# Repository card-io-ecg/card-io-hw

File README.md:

Card/IO hardware
================

Card/IO is an open source, single lead ECG in a business card-like format.

The project contains two PCB designs, created using KiCAD 7:
 
 - main_board: main/carrier board, which is a 4 layer PCB containing the MCU, display, battery and related circuitry
 - frontend: the ECG frontend, ADC, and touch detection/wakeup generator, implemented as a solder-on daughter board

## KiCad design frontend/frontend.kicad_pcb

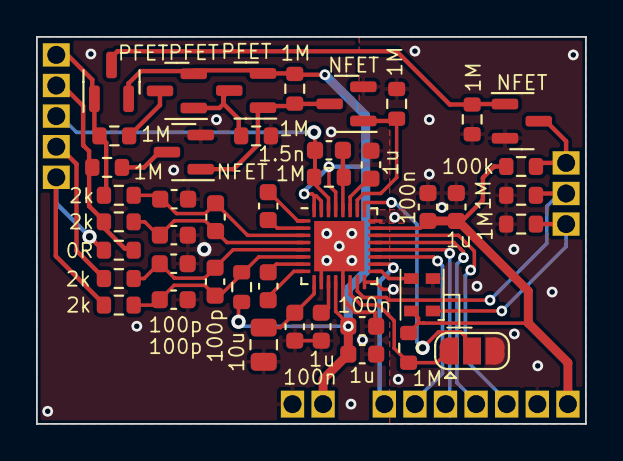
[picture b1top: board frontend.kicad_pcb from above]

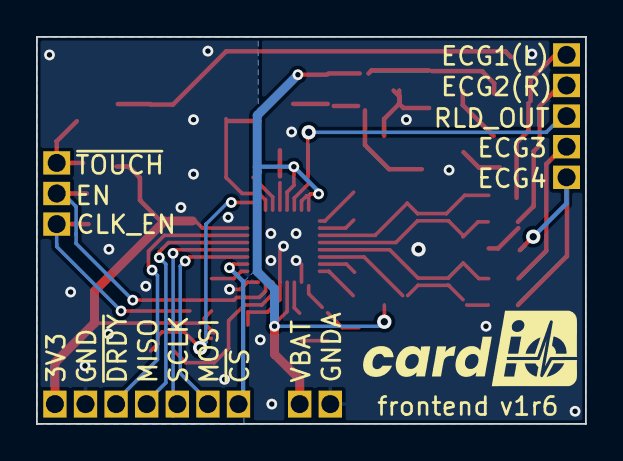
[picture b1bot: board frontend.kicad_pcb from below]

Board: 2 copper layers, 30.5 x 21.5 mm, 57 parts (2 on the bottom side), 36 nets.

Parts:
AVDD1: PAD
AVSS1: PAD
C1, C3, C10: 100n; C_0603_1608Metric
C2, C4, C7, C8: 1u; C_0603_1608Metric
C5, C6: 4.7n; C_0603_1608Metric
C9: 10u; C_0805_2012Metric
C11, C12, C13, C14, C15, C17: 100p; C_0603_1608Metric
C16: 1.5n; C_0603_1608Metric
CLK_EN1: PAD
DGND1: PAD
DVDD1: PAD
ECG1, ECG2, ECG3, ECG4: PAD
G1: logo
JP1: SolderJumper_3_Open; SolderJumper-3_P1.3mm_Open_RoundedPad1.0x1.5mm
MISO1: PAD
MOSI1: PAD
Q1, Q4, Q6: T2N7002AK,LM; SOT-23
Q2, Q3, Q5: NX3008PBK,215; SOT-23
R1, R2, R5, R6: 2k; R_0603_1608Metric
R3, R4, R8, R9, R10, R11, R12, R13, R16, R17: 1M; R_0603_1608Metric
R7, R15: 0R; R_0603_1608Metric
R14: 100k; R_0603_1608Metric
RLD_OUT1: PAD
SCLK1: PAD
U1: ADS1291/2; ADS1291-2
U2: KC2016Z2; KC2016Z

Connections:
+3.3V: C3.1, C4.1, DVDD1.1, R14.2, R17.2, U1.23 (DVDD), U2.4 (VCC)
+BATT: AVDD1.1, C1.1, C2.1, Q2.2 (S), Q3.2 (S), Q5.2 (S), R10.2, R15.1, U1.12 (AVDD), U1.29 (RLDIN/RLDREF), U1.31 (RESP_MODP/IN3P), U1.32 (RESP_MODN/IN3N)
/CLKSEL: JP1.1 (A), R17.1, U1.14 (CLKSEL)
/ECG2P: C14.1, C15.2, R6.2, R15.2, U1.6 (IN2P)
/IO2: JP1.2 (C), U1.25 (GPIO2/RCLK2)
/L: ECG1.1, Q5.1 (G), R1.1, R3.1
/LL: ECG3.1, R5.1
/R: ECG2.1, R2.1, R7.2, R12.2
/R2: ECG4.1, R6.1, R7.1
/TOFF: Q1.3 (D), Q3.1 (G), Q4.1 (G), R10.1
/TOUCH_OFF: Q1.1 (G), R11.2, U1.26 (GPIO1/RCLK1)
/VGND: C16.1, R8.2, RLD_OUT1.1, U1.30 (RLDOUT)
GND: C3.2, C4.2, DGND1.1, JP1.3 (B), Q1.2 (S), Q6.2 (S), R4.1, R11.1, R13.1, R16.1, U1.16 (START), U1.24 (DGND), U2.2 (GND)
GNDA: AVSS1.1, C1.2, C2.2, C7.2, C8.2, C9.2, C10.2, C11.2, C12.2, C13.2, C14.2, Q4.2 (S), R9.1, U1.10 (VREFN), U1.13 (AVSS), U1.33 (PAD/AVSS)
unnamed: Q2.3 (D), R3.2
unnamed: Q2.1 (G), Q3.3 (D), R9.2
unnamed: Q4.3 (D), R12.1
unnamed: Q5.3 (D), Q6.1 (G), R13.2
unnamed: Q6.3 (D), R14.1
unnamed: U1.17 (CLK), U2.3 (CLK)
unnamed: MOSI1.1, U1.19 (DIN)
unnamed: MISO1.1, U1.21 (DOUT)
unnamed: C11.1, C17.1, R1.2, U1.3 (IN1N)
unnamed: C12.1, C17.2, R2.2, U1.4 (IN1P)
unnamed: C13.1, C15.1, R5.2, U1.5 (IN2N)
unnamed: C6.1, U1.1 (PGA1N)
unnamed: C6.2, U1.2 (PGA1P)
unnamed: C5.1, U1.7 (PGA2N)
unnamed: C5.2, U1.8 (PGA2P)
unnamed: C16.2, R8.1, U1.28 (RLDINV)
unnamed: SCLK1.1, U1.20 (SCLK)
unnamed: C7.1, U1.11 (VCAP1)
unnamed: C8.1, U1.27 (VCAP2)
unnamed: C9.1, C10.1, U1.9 (VREFP)
unnamed: R16.2, U1.15 (~PDN/~RESET)
unnamed: CLK_EN1.1, R4.2, U2.1 (INH)

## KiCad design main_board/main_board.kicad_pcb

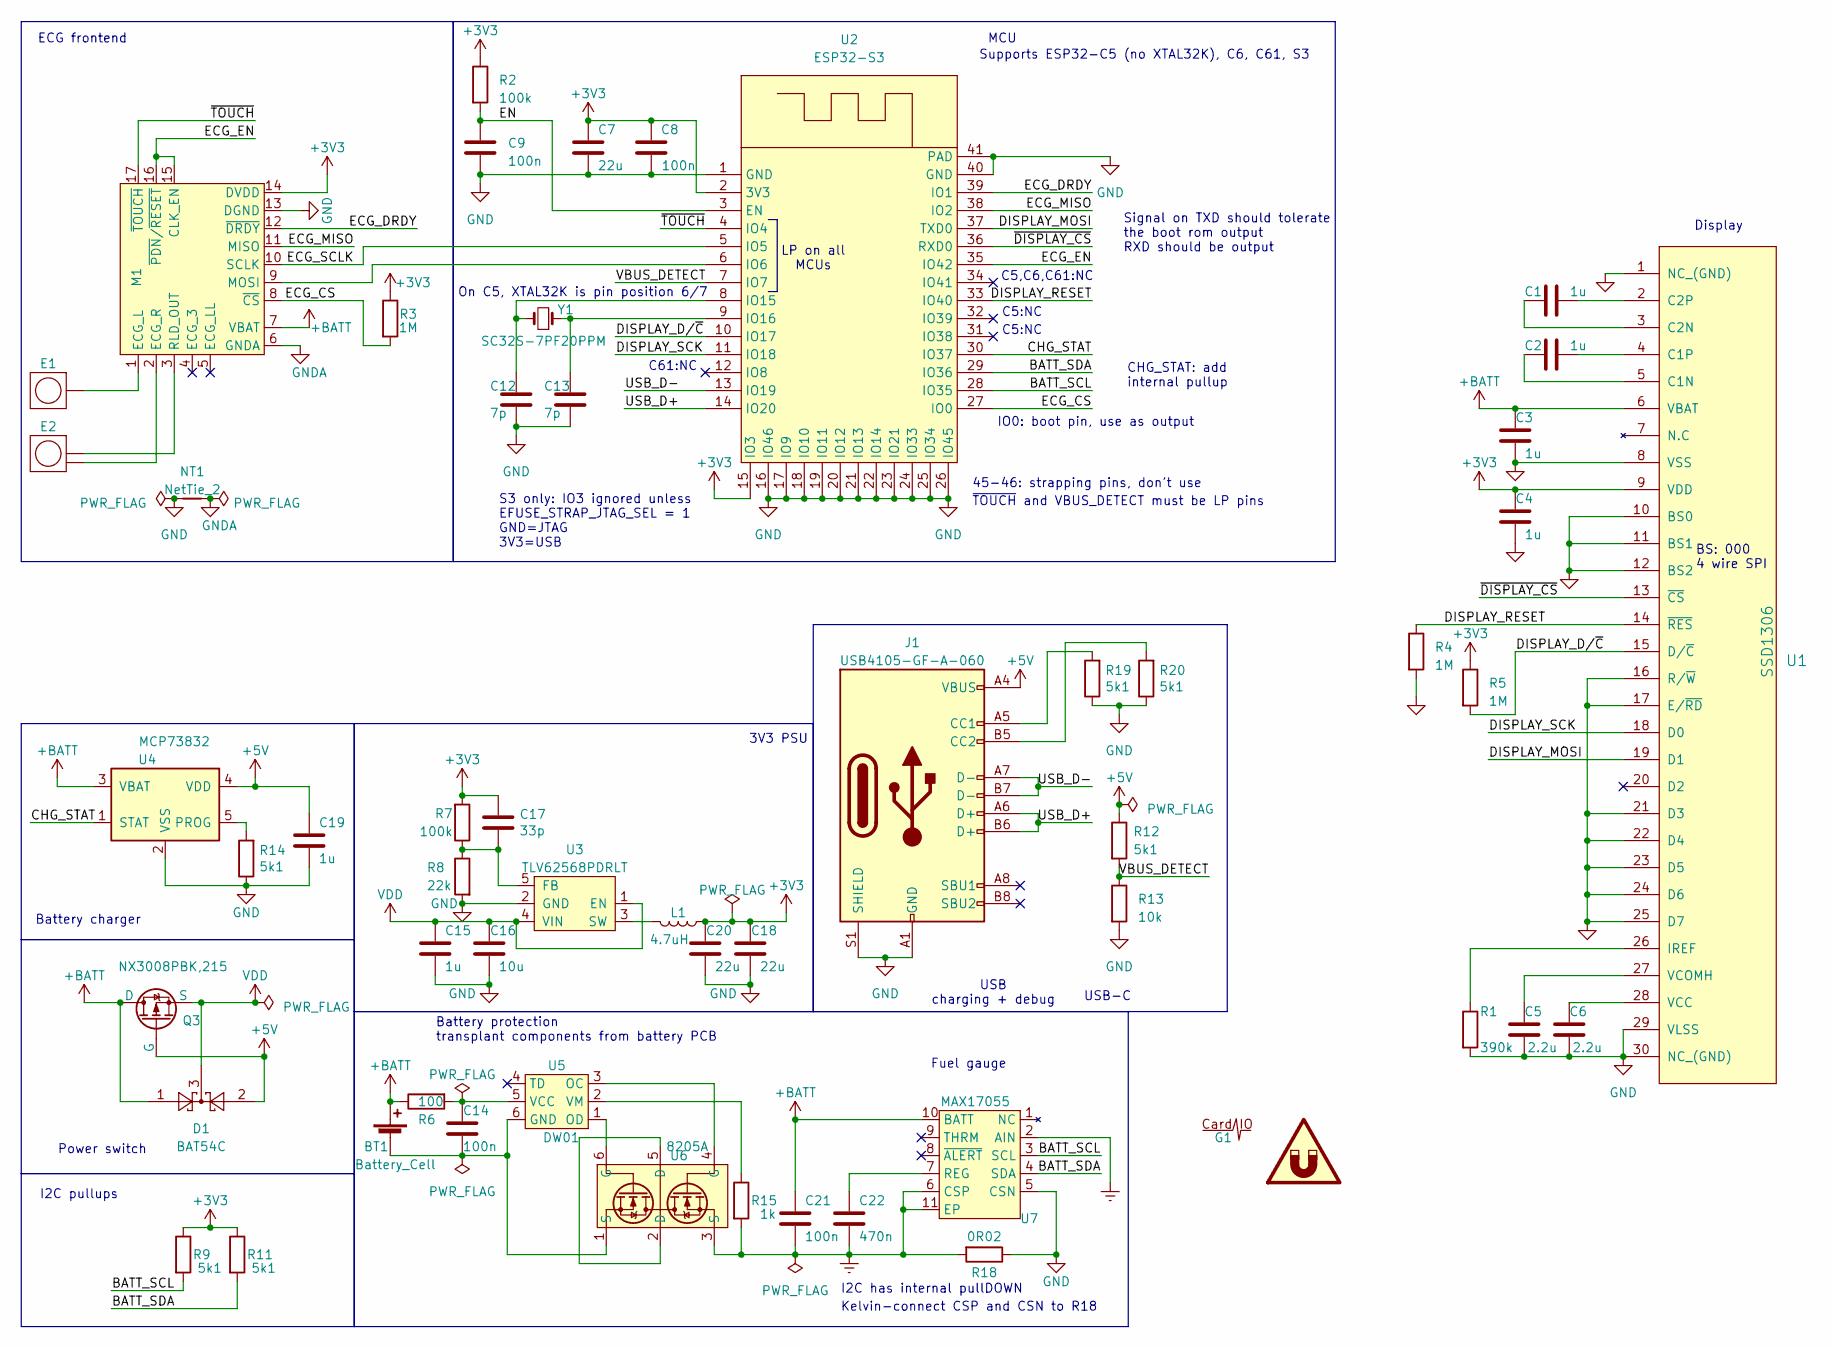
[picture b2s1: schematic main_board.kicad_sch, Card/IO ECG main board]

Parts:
BT1: Battery_Cell; Battery_transplant
C1, C2, C3, C4: 1u; C_0603_1608Metric
C5, C6: 2.2u; C_0603_1608Metric
C7: 22u; C_0805_2012Metric
C8, C9, C14: 100n; C_0603_1608Metric
C12, C13: 7p; C_0603_1608Metric
C15, C19: 1u; C_0603_1608Metric; MPN CL10A105KP8NNWC
C16: 10u; C_0603_1608Metric; MPN JMK107ABJ106MA-T
C17: 33p; C_0603_1608Metric; MPN C0603C330M5HACTU
C18, C20: 22u; C_0805_2012Metric; MPN 0805X226M6R3CT
C21: 100n; C_0603_1608Metric; MPN CL10A105KP8NNWC
C22: 470n; C_0603_1608Metric; MPN CL10A105KP8NNWC
D1: BAT54C; SOT-23
E1: Electrode
E2: SplitElectrode
G1: logo
J1: USB4105-GF-A-060; USB_C_Receptacle_GCT_USB4105-xx-A_16P_TopMnt_Horizontal
L1: 4.7uH; TYA40124R7M-10; MPN TYA40124R7M-10
M1: ECG-module_1lead
NT1: NetTie_2; NetTie-2_SMD_Pad2.0mm
Q3: NX3008PBK,215; SOT-23
QR1: SYM_Magnet_Large; website-qr
R1: 390k; R_0603_1608Metric
R2: 100k; R_0603_1608Metric
R3, R4, R5: 1M; R_0603_1608Metric
R6: 100; R_0603_1608Metric; MPN RC0603FR-072KL
R7: 100k; R_0603_1608Metric; MPN RC0603JR-07100KL
R8: 22k; R_0603_1608Metric; MPN RC0603FR-0722KL
R9, R11, R12: 5k1; R_0603_1608Metric
R13: 10k; R_0603_1608Metric
R14, R19, R20: 5k1; R_0603_1608Metric; MPN RC0603FR-072KL
R15: 1k; R_0603_1608Metric
R18: 0R02; R_0603_1608Metric
U1: SSD1306
U2: ESP32-S3; ESP32-WROOM-1-COMBO
U3: TLV62568PDRLT; SOT-23-5
U4: MCP73832; SOT-23-5
U5: DW01; SOT-23-6
U6: 8205A; SOT-23-6
U7: MAX17055
Y1: SC32S-7PF20PPM; Crystal_SMD_MicroCrystal_CC7V-T1A-2Pin_3.2x1.5mm

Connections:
+3V3: C4.2, C7.1, C8.1, C17.1, C18.1, C20.1, L1.1, M1.14 (DVDD), R2.1, R3.1, R5.1, R7.2, R9.1, R11.1, U1.9 (VDD), U2.2 (3V3), U2.15 (IO3)
+5V: C19.1, D1.2, J1.A4 (VBUS), J1.A9 (VBUS), J1.B4 (VBUS), J1.B9 (VBUS), Q3.1 (G), R12.1, U4.4 (VDD)
+BATT: BT1.1 (+), C3.2, C21.1, D1.1, M1.7 (VBAT), Q3.3 (D), R6.1, U1.6 (VBAT), U4.3 (VBAT), U7.10 (BATT)
/BATT_SCL: R9.2, U2.28 (IO35), U7.3 (SCL)
/BATT_SDA: R11.2, U2.29 (IO36), U7.4 (SDA)
/CHG_STAT: U2.30 (IO37), U4.1 (STAT)
/DISPLAY_D/~C: R5.2, U1.15 (D/~C), U2.10 (IO17)
/DISPLAY_MOSI: U1.19 (D1), U2.37 (TXD0)
/DISPLAY_RESET: R4.1, U1.14 (~RES), U2.33 (IO40)
/DISPLAY_SCK: U1.18 (D0), U2.11 (IO18)
/ECG_CS: M1.8 (~CS), R3.2, U2.27 (IO0)
/ECG_DRDY: M1.12 (~DRDY), U2.39 (IO1)
/ECG_EN: M1.15 (CLK_EN), M1.16 (~PDN/~RESET), U2.35 (IO42)
/ECG_MISO: M1.11 (MISO), U2.38 (IO2)
/ECG_SCLK: M1.10 (SCLK), U2.5 (IO5)
/EN: C9.1, R2.2, U2.3 (EN)
/USB_D+: J1.A6 (D+), J1.B6 (D+), U2.14 (IO20)
/USB_D-: J1.A7 (D-), J1.B7 (D-), U2.13 (IO19)
/VBUS_DETECT: R12.2, R13.1, U2.7 (IO7)
/~DISPLAY_CS: U1.13 (~CS), U2.36 (RXD0)
/~TOUCH: M1.17 (~TOUCH), U2.4 (IO4)
Earth: C21.2, C22.2, R15.2, R18.2, U6.3 (S), U7.2 (AIN), U7.6 (CSP), U7.11 (EP)
GND: C3.1, C4.1, C5.1, C6.1, C7.2, C8.2, C9.2, C12.1, C13.1, C15.2, C16.2, C18.2, C19.2, C20.2, J1.A1 (GND), J1.A12 (GND), J1.B1 (GND), J1.B12 (GND), J1.S1 (SHIELD), M1.13 (DGND), NT1.1, R1.2, R4.2, R8.2, R13.2, R14.1, R18.1, R19.1, R20.1, U1.1 (NC_(GND)), U1.8 (VSS), U1.10 (BS0), U1.11 (BS1), U1.12 (BS2), U1.16 (R/~W), U1.17 (E/~RD), U1.21 (D3), U1.22 (D4), U1.23 (D5), U1.24 (D6), U1.25 (D7), U1.29 (VLSS), U1.30 (NC_(GND)), U2.1 (GND), U2.16 (IO46), U2.17 (IO9), U2.18 (IO10), U2.19 (IO11), U2.20 (IO12), U2.21 (IO13), U2.22 (IO14), U2.23 (IO21), U2.24 (IO33), U2.25 (IO34), U2.26 (IO45), U2.40 (GND), U2.41 (PAD), U3.2 (GND), U4.2 (VSS), U7.5 (CSN)
GNDA: M1.6 (GNDA), NT1.2
unnamed: BT1.2 (-), C14.2, U5.6 (GND), U6.1 (S)
unnamed: J1.A5 (CC1), R19.2
unnamed: J1.B5 (CC2), R20.2
unnamed: E1.1, M1.1 (ECG_L)
unnamed: E2.2, M1.2 (ECG_R)
unnamed: M1.9 (MOSI), U2.6 (IO6)
unnamed: E2.1, M1.3 (RLD_OUT)
unnamed: C2.1, U1.5 (C1N)
unnamed: C2.2, U1.4 (C1P)
unnamed: C1.1, U1.3 (C2N)
unnamed: C1.2, U1.2 (C2P)
unnamed: R1.1, U1.26 (IREF)
unnamed: C6.2, U1.28 (VCC)
unnamed: C5.2, U1.27 (VCOMH)
unnamed: C12.2, U2.8 (IO15), Y1.2
unnamed: C13.2, U2.9 (IO16), Y1.1
unnamed: C17.2, R7.1, R8.1, U3.5 (FB)
unnamed: L1.2, U3.3 (SW)
unnamed: R14.2, U4.5 (PROG)
unnamed: U5.3 (OC), U6.4 (G)
unnamed: U5.1 (OD), U6.6 (G)
unnamed: C14.1, R6.2, U5.5 (VCC)
unnamed: R15.1, U5.2 (VM)
unnamed: U6.2 (D), U6.5 (D)
unnamed: C22.1, U7.7 (REG)
VDD: C15.1, C16.1, D1.3, Q3.2 (S), U3.1 (EN), U3.4 (VIN)

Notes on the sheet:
IO0: boot pin, use as output
Supports ESP32-C5 (no XTAL32K), C6, C61, S3
Signal on TXD should tolerate the boot rom output RXD should be output
USB-C
On C5, XTAL32K is pin position 6/7
LP on all MCUs
ECG frontend
C5:NC
Kelvin-connect CSP and CSN to R18
C5,C6,C61:NC
MCU
Battery charger
CHG_STAT: add internal pullup
Fuel gauge
~{TOUCH} and VBUS_DETECT must be LP pins
3V3 PSU
BS: 000 4 wire SPI
45-46: strapping pins, don't use
I2C has internal pullDOWN
Battery protection transplant components from battery PCB
I2C pullups
Display
S3 only: IO3 ignored unless EFUSE_STRAP_JTAG_SEL = 1 GND=JTAG 3V3=USB
Power switch
C61:NC
USB charging + debug

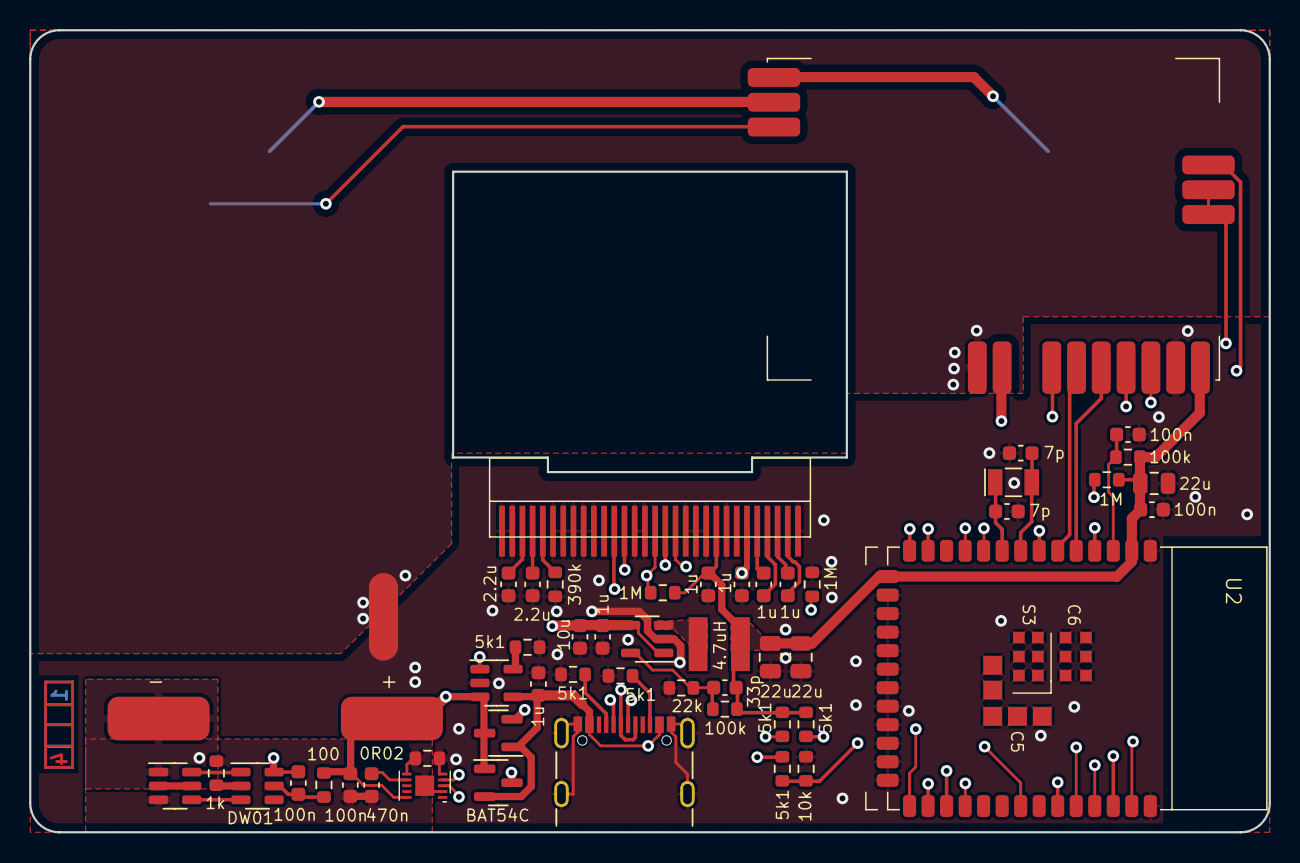
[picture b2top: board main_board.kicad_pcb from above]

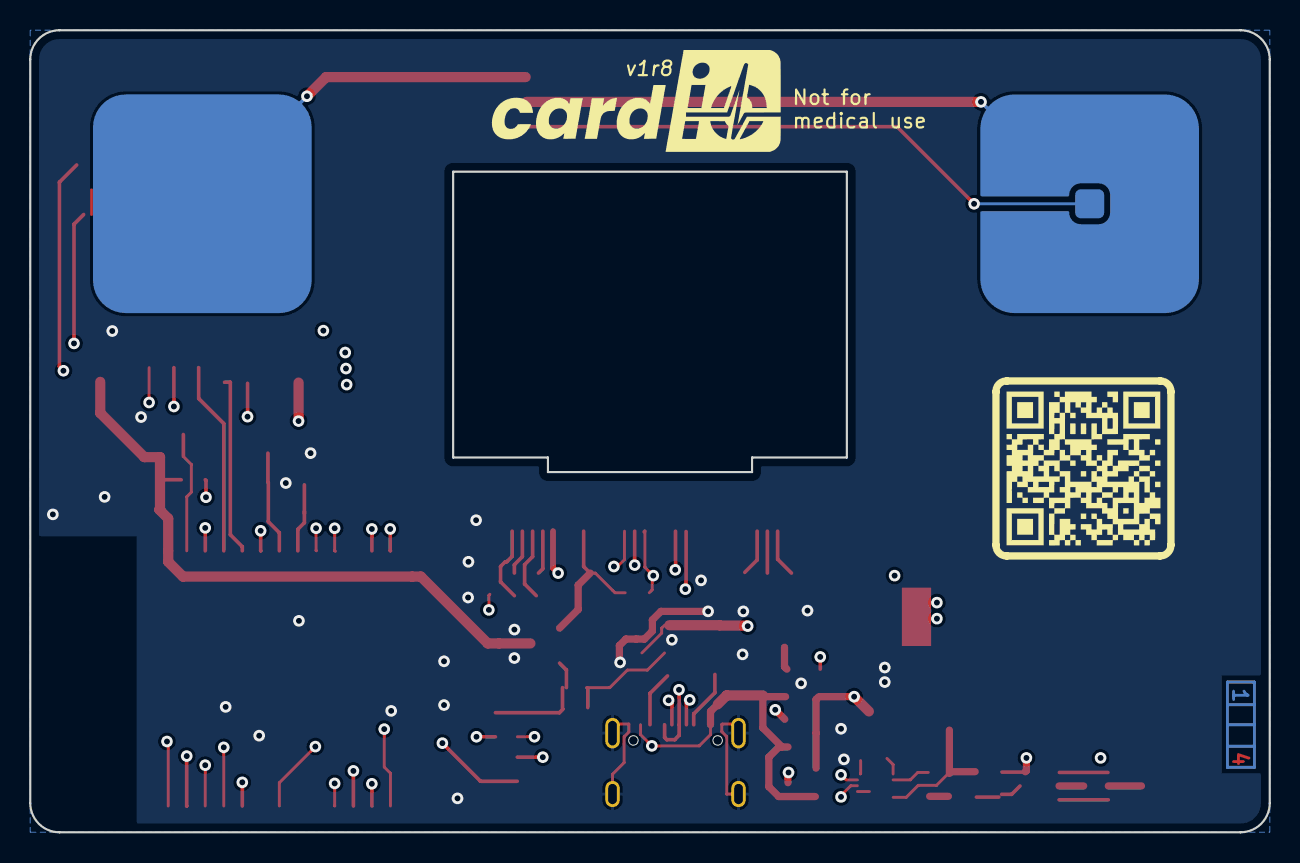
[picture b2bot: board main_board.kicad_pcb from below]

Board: 4 copper layers, 85.0 x 55.0 mm, 56 parts (4 on the bottom side), 50 nets.

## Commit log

2023-04-27 Correct battery charger
2023-04-27 Specify KiCad
2023-05-11 Fix #4: Remove IO0 pullup
2023-05-11 Enlarge keepout zone
2023-05-11 Fix #7: move battery
2023-05-11 Allow reading back CLKSEL
2023-05-19 Fix #11: remove filters
2023-05-19 Fix #5: tune touch detector resistors
2023-05-19 Fix #8: add input to disable oscillator
2023-05-19 Update frontend layout
2023-05-22 Fix #17: Move display cutout
2023-05-22 Fix #12: add PFET
2023-05-22 Fix #18: add RLD output, fix main board revision
2023-05-23 Add clken to symbol, connect to MCU
2023-05-23 Add changes to layout
2023-05-25 Fix #19: shuffle pin assignment
2023-05-25 Fix #16: move JTAG to front side
2023-05-25 Tweak routing a bit
2023-05-25 Place battery terminals directly onto PCB
2023-05-26 Close #15: add battery protection components
2023-05-26 Add more output capacitance to DC/DC
2023-05-26 Move electrodes a bit
2023-05-26 Move frontend away from the edge
2023-05-27 Tweak frontend routing
2023-06-01 Fix #24: move VBUS detect to IO17
2023-06-01 Add logo
2023-06-01 Fix #21: Add split electrodes
2023-06-02 Fix #3: add QR code, exclude some parts from BOM
2023-06-03 Close #25: Add MAX17055
2023-06-03 Close #10: move ESP from board edge
2023-06-04 Add logo to daughter board
2023-06-04 Add component values to daugther board
2023-06-04 Update 3d model
2023-06-04 Fix pad positions
2023-06-04 Add component values to main board
2023-06-04 Small tweaks
2023-06-04 Tweak schematic a bit
2023-06-05 Close #23: supply MCU from charger
2023-06-05 Additional minor tweaks
2023-06-05 Close #26: add new logo
2023-06-05 Tweak frontend layout
2023-06-16 Fix #29: fix frontend PCB pad assignment
2023-06-16 Correct current sense value
2023-06-16 Correct charge current resistor value
2023-06-16 Remove unused metadata
2023-06-16 Close #27: unify footprints
2023-06-16 Update no-bom metadata
2023-06-16 Fix label positions
2023-07-19 Remove battery ADC parts, simplify and tweak routing, add locking holes to jtag
2023-08-11 Add 3d models
2023-08-11 Correct USB clipping into the board
2023-08-11 Add enclosure design
2023-08-13 Increase wall height
2023-08-24 Tweak display cutout
2023-08-24 Remove default link from jtag selector
2023-08-24 Remove JTAG silk screen
2023-08-24 Replace USB with USB4105-GF-A-060
2023-08-24 Update enclosure
2023-08-24 Finalize v1r4
2023-09-07 Tweak enclosure
2023-09-08 Close #31: tweak touch detection
2023-09-08 Close #32: Add missing silk screen
2023-09-08 Close #33: Clean up RLD
2023-09-08 Clean up
2023-09-08 Tweak split electrode
2023-09-08 Ignore bom and fabrication folders
2023-09-11 Tweak touch detector circuit
2023-09-18 Shrink frontend a bit
2023-10-01 Fix rule violation, use a single plane on front side
2023-10-07 Add second channel components
2023-11-03 Remove JTAG selector
2023-11-03 Replace battery alert input with ADC_EN
2023-11-03 Move frontend chip select to IO0
2023-11-03 Remove JTAG port
2023-11-03 Move display SPI to the right side of the module
2023-11-04 Tweak routing
2023-11-04 Tweak frontend
2023-11-04 Finalize frontend
2023-11-04 Enlarge electrodes
2023-11-04 Final tweaks: switch ch2 electrodes
2023-11-05 Separate frontend reset from system enable
2023-11-14 Add a note about LP GPIO ranges
2023-11-14 Fix #36: swap VBUS_DETECT and DISPLAY_CS
2023-11-17 Keep fuel gauge comm lines pulled up
2023-11-20 Label the serial debug port, add strapping pullup
2023-11-20 Pull up D/C instead of CS
2023-11-22 Move VBUS_DETECT to a LP_IO pin
2023-12-05 Annotate C6 pins
2024-09-21 Remove useless serial port
2025-11-30 Update to kicad 9
2025-11-30 Add C5/C61 options, mark as rev7
2025-12-17 Document C5 32k xtal difference
2025-12-20 r8: fix main board issues, update frontend clksel
